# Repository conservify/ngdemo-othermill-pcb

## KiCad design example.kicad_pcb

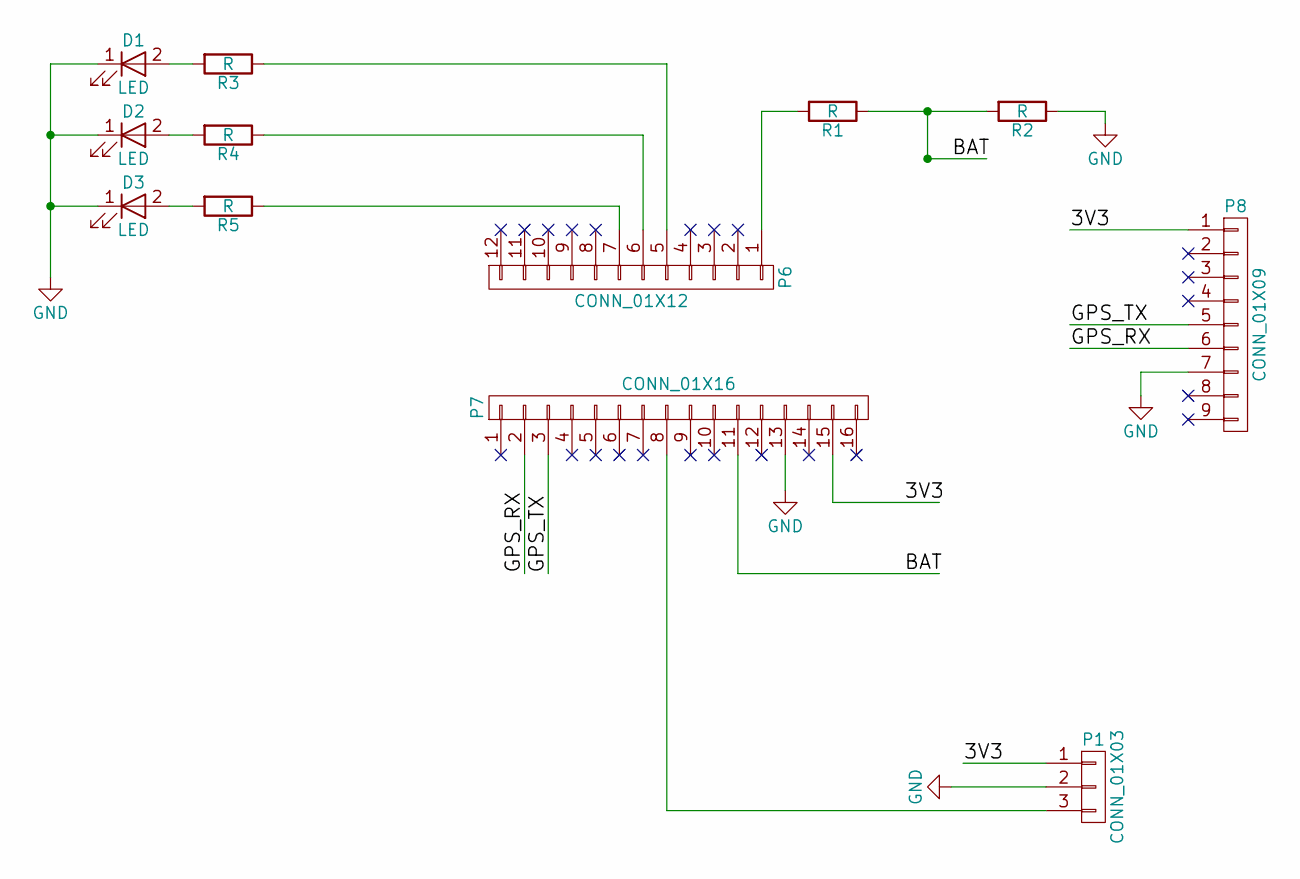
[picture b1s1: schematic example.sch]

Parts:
D1, D2, D3: LED; D_T-1_P2.54mm_Vertical_AnodeUp
P1: CONN_01X03; Socket_Strip_Straight_1x03
P6: CONN_01X12; Socket_Strip_Straight_1x12
P7: CONN_01X16; Socket_Strip_Straight_1x16
P8: CONN_01X09; Socket_Strip_Straight_1x09
R1, R2: R; Resistor_Horizontal_RM7mm
R3, R4, R5: R; R_Axial_DIN0207_L6.3mm_D2.5mm_P7.62mm_Horizontal

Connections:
/3V3: P1.1, P7.15, P8.1
/BAT: P7.11, R1.1, R2.2
/GPS_RX: P7.2, P8.6
/GPS_TX: P7.3, P8.5
GND: D1.1 (K), D2.1 (K), D3.1 (K), P1.2, P7.13, P8.7, R2.1
unnamed: D1.2 (A), R3.2
unnamed: D2.2 (A), R4.2
unnamed: D3.2 (A), R5.2
unnamed: P1.3, P7.8
unnamed: P6.1, R1.2
unnamed: P6.5, R3.1
unnamed: P6.6, R4.1
unnamed: P6.7, R5.1

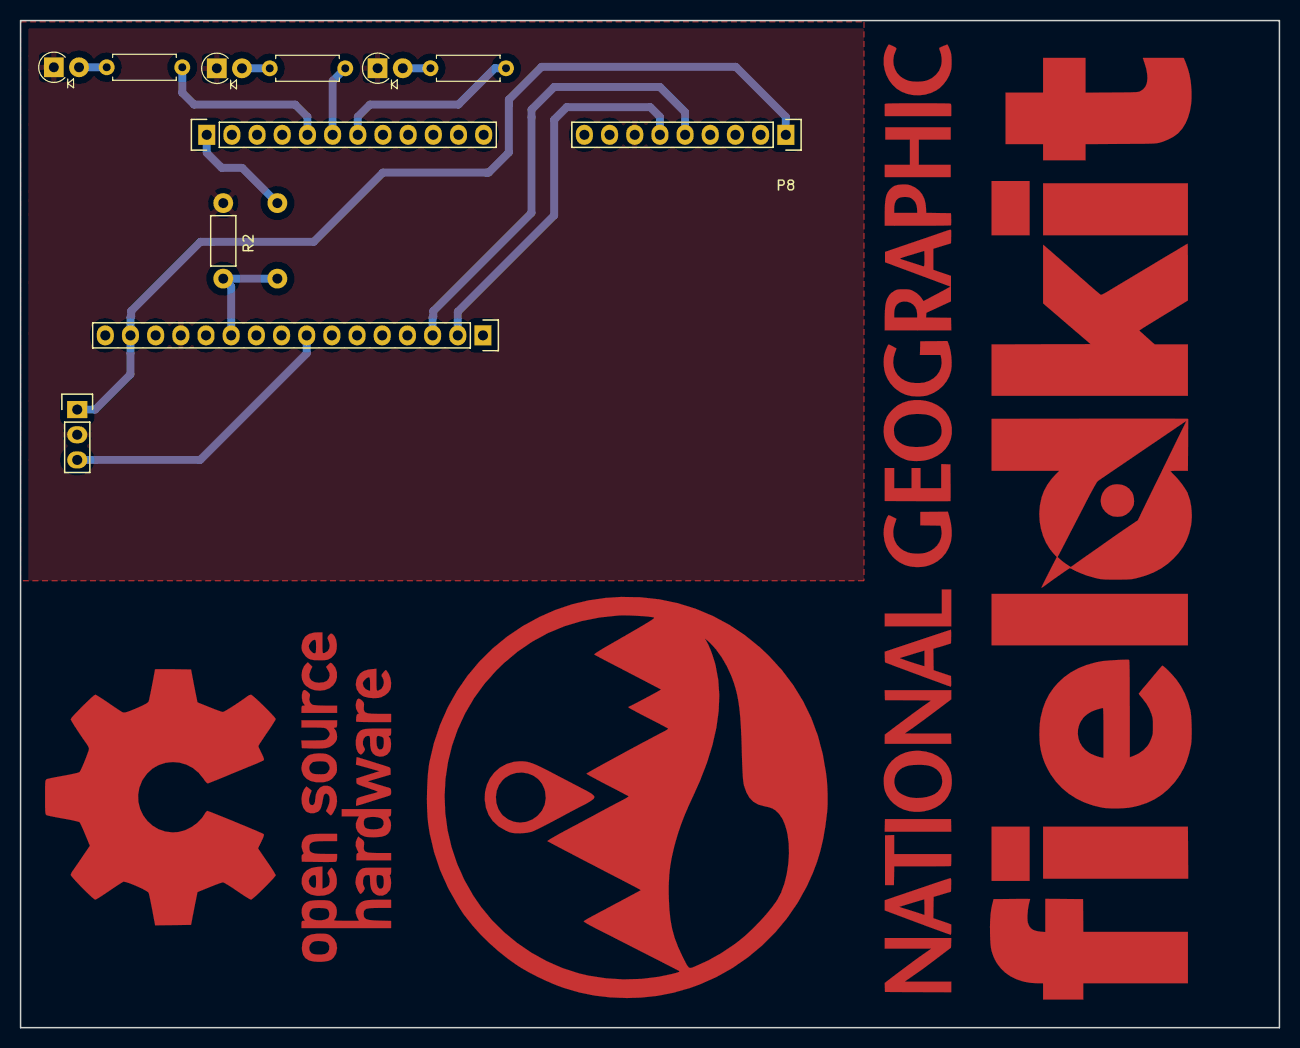
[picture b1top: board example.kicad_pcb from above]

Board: 2 copper layers, 127.0 x 101.6 mm, 12 parts (1 on the bottom side), 13 nets.

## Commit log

2017-01-11 Checkpoint before trying to rotate the GPS.
2017-01-12 Saving PCB.
2017-01-19 Some rename/cleanup before pushing to github.
2017-03-28 Adjust for wifi board for April demo.
2017-03-28 Add some LEDs for status indicators.
2017-03-30 Nudge circuit inwards.
2017-03-30 Kicad should regenerate fills before a plot.
2017-03-31 Add a hole to feed the battery cable through.
2017-03-31 Drop the charging board, it's unnecessary. Make sensor a legit conn.
